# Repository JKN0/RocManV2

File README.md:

# RocMan V2

A Pacman game built using a junk RGB led matrix, 88x88 pixels

Controlled by junk IR remote

CPU is Chinese 8051 variant STC8A8K64D4

This is built on PCB, minor I/O-pin changes in SW compared to V1

There are two versions of PCB:
 - V2.0: original PCB
 - V2.1: connectors for USB/serial adapter and analog joystick added
 
Software is the same for both PCBs.

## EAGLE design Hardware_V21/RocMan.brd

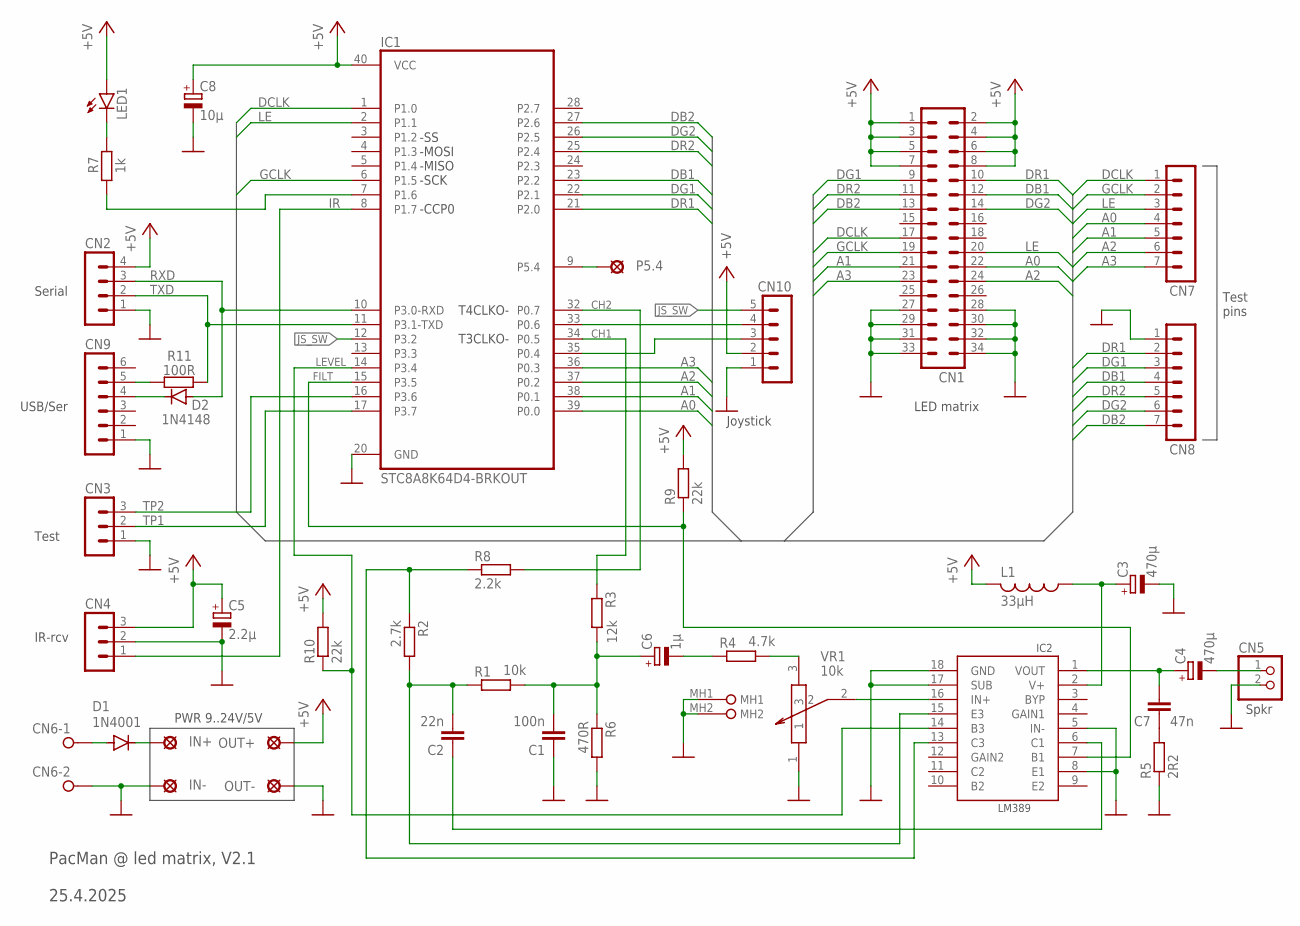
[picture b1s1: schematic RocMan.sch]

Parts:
C1: 100n; C0805
C2: 22n; C0805
C3, C4: 470μ; E5-10,5
C5: 2.2μ; SMC_A
C6: 1μ; SMC_A
C7: 47n; C0805
C8: 10μ; SMC_A
CN1: ML34
CN2: MA04-1
CN3, CN4: MA03-1
CN5: PINHD-1X2; 1X02
CN6: W237-02P; W237-132
CN7, CN8: MA07-1
CN9: MA06-1
CN10: MA05-1
D1: 1N4001; DO41-10
D2: 1N4148; SOD123
IC1: STC8A8K64D4-BRKOUT; DIL40
IC2: LM389; DIL18
IN+: LSP11
IN-: LSP11
L1: 33μH; L4532M
LED1: LEDCHIP-LED0805; CHIP-LED0805
OUT+: LSP11
OUT-: LSP11
P5.4: LSP11
R1: 10k; R0805
R2: 2.7k; R0805
R3: 12k; R0805
R4: 4.7k; R0805
R5: 2R2; R0805
R6: 470R; R0805
R7: 1k; R0805
R8: 2.2k; R0805
R9, R10: 22k; R0805
R11: 100R; R0805
VR1: 10k; PTV09A4015FA103

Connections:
+5V: C5.+, C8.+, CN1.1, CN1.2, CN1.3, CN1.4, CN1.5, CN1.6, CN1.7, CN1.8, CN2.4, CN4.3, CN10.2, IC1.40 (VCC), L1.2, LED1.A, OUT+.MP, R9.2, R10.2
A0: CN1.22, CN7.4, IC1.39 (P0.0)
A1: CN1.21, CN7.5, IC1.38 (P0.1)
A2: CN1.24, CN7.6, IC1.37 (P0.2)
A3: CN1.23, CN7.7, IC1.36 (P0.3)
CH1: IC1.34 (P0.5), R3.1
CH2: IC1.32 (P0.7), R8.2
DB1: CN1.12, CN8.4, IC1.23 (P2.2)
DB2: CN1.13, CN8.7, IC1.27 (P2.6)
DCLK: CN1.17, CN7.1, IC1.1 (P1.0)
DG1: CN1.9, CN8.3, IC1.22 (P2.1)
DG2: CN1.14, CN8.6, IC1.26 (P2.5)
DR1: CN1.10, CN8.2, IC1.21 (P2.0)
DR2: CN1.11, CN8.5, IC1.25 (P2.4)
FILT: IC1.15 (P3.5), IC2.7 (B1), R9.1
GCLK: CN1.19, CN7.2, IC1.6 (P1.5)
GND: C1.1, C3.-, C5.-, C8.-, CN1.27, CN1.28, CN1.29, CN1.30, CN1.31, CN1.32, CN1.33, CN1.34, CN2.1, CN3.1, CN4.2, CN5.2, CN6.2, CN8.1, CN9.1, CN10.1, IC1.20 (GND), IC2.5 (IN-), IC2.8 (E1), IC2.17 (SUB), IC2.18 (GND), IN-.MP, OUT-.MP, R5.1, R6.2, VR1.1, VR1.MH1, VR1.MH2
IR: CN4.1, IC1.8 (P1.7)
JS_SW: CN10.5, IC1.12 (P3.2)
LE: CN1.20, CN7.3, IC1.2 (P1.1)
LEVEL: IC1.14 (P3.4), IC2.14 (B3), R10.1
unnamed: C2.2, IC2.15 (E3), R1.1, R2.2
unnamed: C1.2, C6.+, R1.2, R3.2, R6.1
unnamed: C2.1, IC2.6 (C1)
unnamed: C6.-, R4.1
unnamed: R4.2, VR1.3
unnamed: IC2.13 (C3), R2.1, R8.1
unnamed: IC2.16 (IN+), VR1.2
unnamed: C3.+, IC2.2 (V+), L1.1
unnamed: CN6.1, D1.A
unnamed: C4.+, C7.2, IC2.1 (VOUT)
unnamed: C4.-, CN5.1
unnamed: D1.C, IN+.MP
unnamed: C7.1, R5.2
unnamed: IC1.7 (P1.6), R7.1
unnamed: LED1.C, R7.2
unnamed: CN9.5, R11.1
unnamed: CN9.4, D2.C
unnamed: CN10.4, IC1.33 (P0.6)
unnamed: CN10.3, IC1.35 (P0.4)
unnamed: IC1.9 (P5.4), P5.4.MP
RXD: CN2.3, D2.A, IC1.10 (P3.0-RXD)
TP1: CN3.2, IC1.17 (P3.7)
TP2: CN3.3, IC1.16 (P3.6)
TXD: CN2.2, IC1.11 (P3.1-TXD), R11.2

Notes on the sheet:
-SS -MOSI -MISO -SCK
-CCP0
Serial
Test
T4CLKO- T3CLKO-
IR-rcv
Spkr
PacMan @ led matrix, V2.1 25.4.2025
LED matrix
PWR 9..24V/5V
Test pins
USB/Ser
Joystick

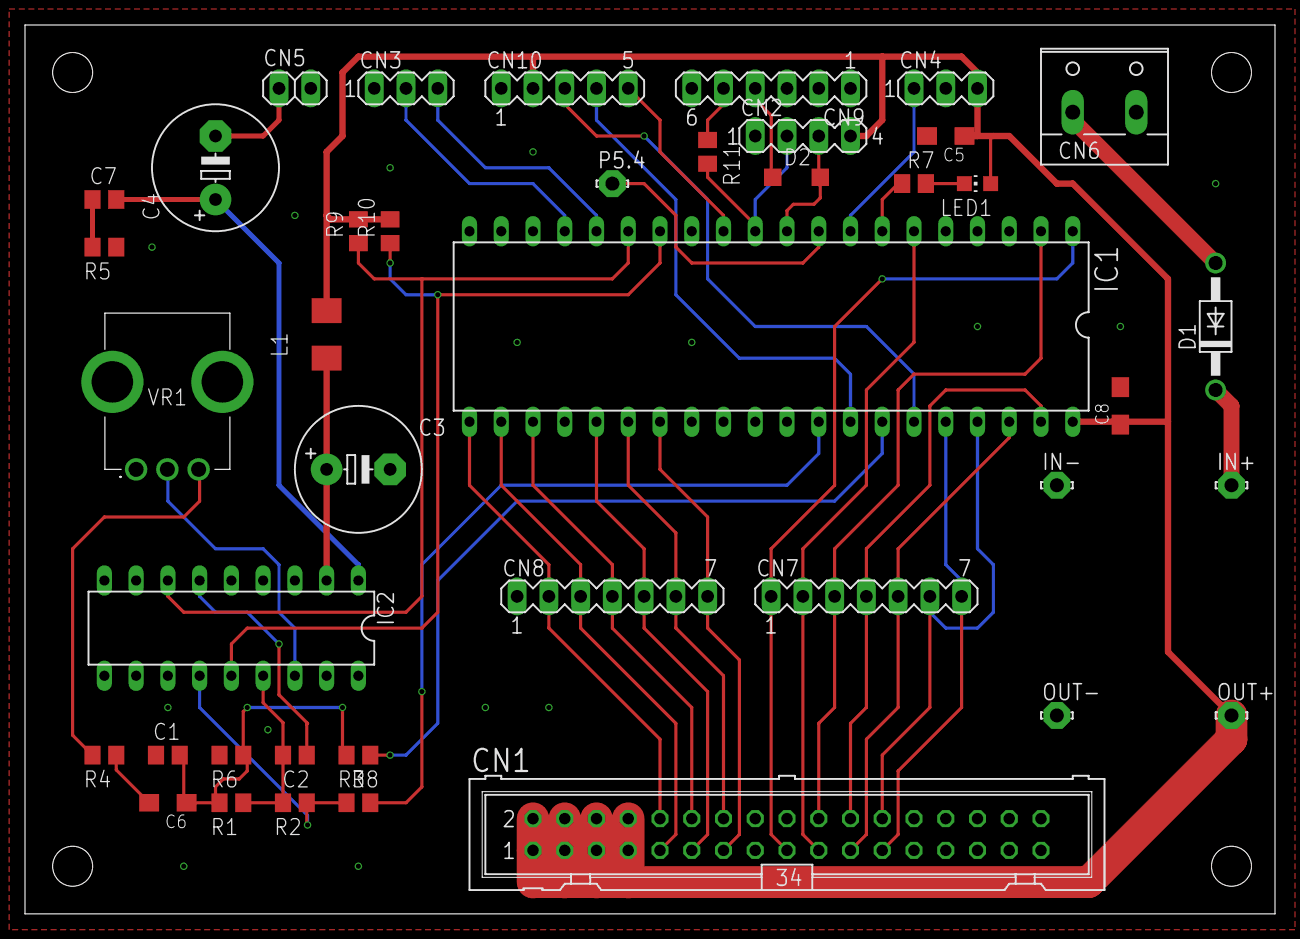
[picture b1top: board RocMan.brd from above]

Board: 2 copper layers, 100.0 x 71.1 mm, 41 parts (0 on the bottom side), 45 nets.

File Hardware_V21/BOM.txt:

Qty Value              Device             Package         Parts                Description                          
1   STC8A8K64D4-BRKOUT STC8A8K64D4-BRKOUT DIL40           IC1                  STC8A8K64D4/QFP48 @ DIP-40 breakout  
1                      LM389              DIL18           IC2                  Audio amp + 3 transistors            
1   1N4001             1N4004             DO41-10         D1                   DIODE
1   1N4148             1N4148             SOD-123         D2                   DIODE
1                      LEDCHIP-LED0805    CHIP-LED0805    LED1                 LED                                  0603
1                      ML34               ML34            CN1                  PIN HEADER FEMALE 2x17               
1                      MA04-1             MA04-1          CN2                  PIN HEADER 1x4                       
2                      MA03-1             MA03-1          CN3, CN4             PIN HEADER 1x3                       
1                      PINHD-1X2          1X02            CN5                  PIN HEADER 1x2                       
2                                                                              PIN HEADER FEMALE 1x20 (for IC1)     
1                      W237-02P           W237-132        CN6                  SREW CLAMP                           
2                      MA07-1             MA07-1          CN7, CN8             PIN HEADER 1x7                       
1                      MA06-1             MA06-1          CN9                  PIN HEADER 1x6                       
1                      MA05-1             MA05-1          CN10                 PIN HEADER 1x5                       
1   100n               C-EUC0805          C0805           C1                   CAPACITOR                            
1   22n                C-EUC0805          C0805           C2                   CAPACITOR                            
2   470μ               CPOL-EUE5-10.5     E5-10,5         C3, C4               POLARIZED CAPACITOR                  
1   2.2μ               CPOL-EUSMCA        SMC_A           C5                   POLARIZED CAPACITOR                  
1   1μ                 CPOL-EUSMCA        SMC_A           C6                   POLARIZED CAPACITOR                  
1   47n                C-EUC0805          C0805           C7                   CAPACITOR                            
1   10μ                CPOL-EUSMCA        SMC_A           C8                   POLARIZED CAPACITOR                  use 4.7μ
1   10k                R-EU_R0805         R0805           R1                   RESISTOR                             
1   2.7k               R-EU_R0805         R0805           R2                   RESISTOR                             
1   12k                R-EU_R0805         R0805           R3                   RESISTOR                             
1   4.7k               R-EU_R0805         R0805           R4                   RESISTOR                             
1   1k                 R-EU_R0805         R0805           R7                   RESISTOR                             
1   2R2                R-EU_R0805         R0805           R5                   RESISTOR                             
1   470R               R-EU_R0805         R0805           R6                   RESISTOR                             
1   2.2k               R-EU_R0805         R0805           R8                   RESISTOR                             
2   22k                R-EU_R0805         R0805           R9, R10              RESISTOR                             use 20k
1   100R               R-EU_R0805         R0805           R11                  RESISTOR                             
1   10k                PTV09A-4015F-A103  PTV09A4015FA103 VR1                  Pot 10K AUDIO 20%                    
1   33μH               L-USL4532C         L4532M          L1                   INDUCTOR                             
1                      Pwr supply module                                       Pwr 9...24V/5V                       
1   TSOP34838          IR receiver                                                                                  
1   PCB

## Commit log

2025-03-29 Pacman on junk led matrix & 8051
2025-04-11 Added hex-file
2025-04-11 Add support for couple of junk IR remotes
2025-04-16 Added BOM
2025-04-25 Added V2.1 schema
2025-04-28 Final V2.1 HW
